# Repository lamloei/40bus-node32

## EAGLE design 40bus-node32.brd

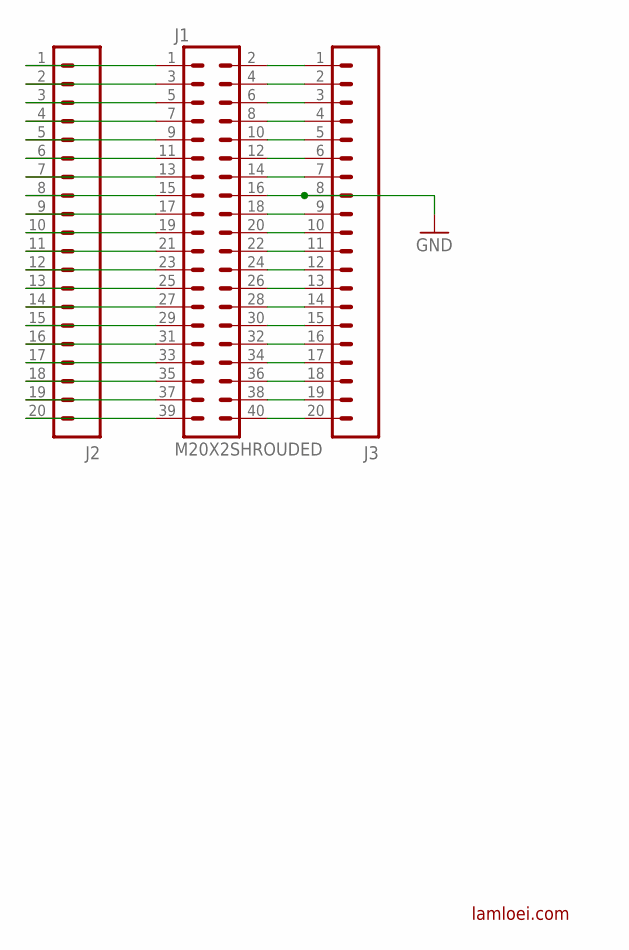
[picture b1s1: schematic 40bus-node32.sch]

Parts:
J1: M20X2SHROUDED; 2X20_SHROUDED
J2, J3: M20; 1X20
U$1: LAMLEOI_LOGO_3

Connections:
GND: J1.16, J3.8
unnamed: J1.2, J3.1
unnamed: J1.4, J3.2
unnamed: J1.6, J3.3
unnamed: J1.8, J3.4
unnamed: J1.10, J3.5
unnamed: J1.12, J3.6
unnamed: J1.14, J3.7
unnamed: J1.18, J3.9
unnamed: J1.20, J3.10
unnamed: J1.22, J3.11
unnamed: J1.24, J3.12
unnamed: J1.26, J3.13
unnamed: J1.28, J3.14
unnamed: J1.30, J3.15
unnamed: J1.32, J3.16
unnamed: J1.34, J3.17
unnamed: J1.36, J3.18
unnamed: J1.38, J3.19
unnamed: J1.40, J3.20
unnamed: J1.1, J2.1
unnamed: J1.3, J2.2
unnamed: J1.5, J2.3
unnamed: J1.7, J2.4
unnamed: J1.9, J2.5
unnamed: J1.11, J2.6
unnamed: J1.13, J2.7
unnamed: J1.15, J2.8
unnamed: J1.17, J2.9
unnamed: J1.19, J2.10
unnamed: J1.21, J2.11
unnamed: J1.23, J2.12
unnamed: J1.25, J2.13
unnamed: J1.27, J2.14
unnamed: J1.29, J2.15
unnamed: J1.31, J2.16
unnamed: J1.33, J2.17
unnamed: J1.35, J2.18
unnamed: J1.37, J2.19
unnamed: J1.39, J2.20

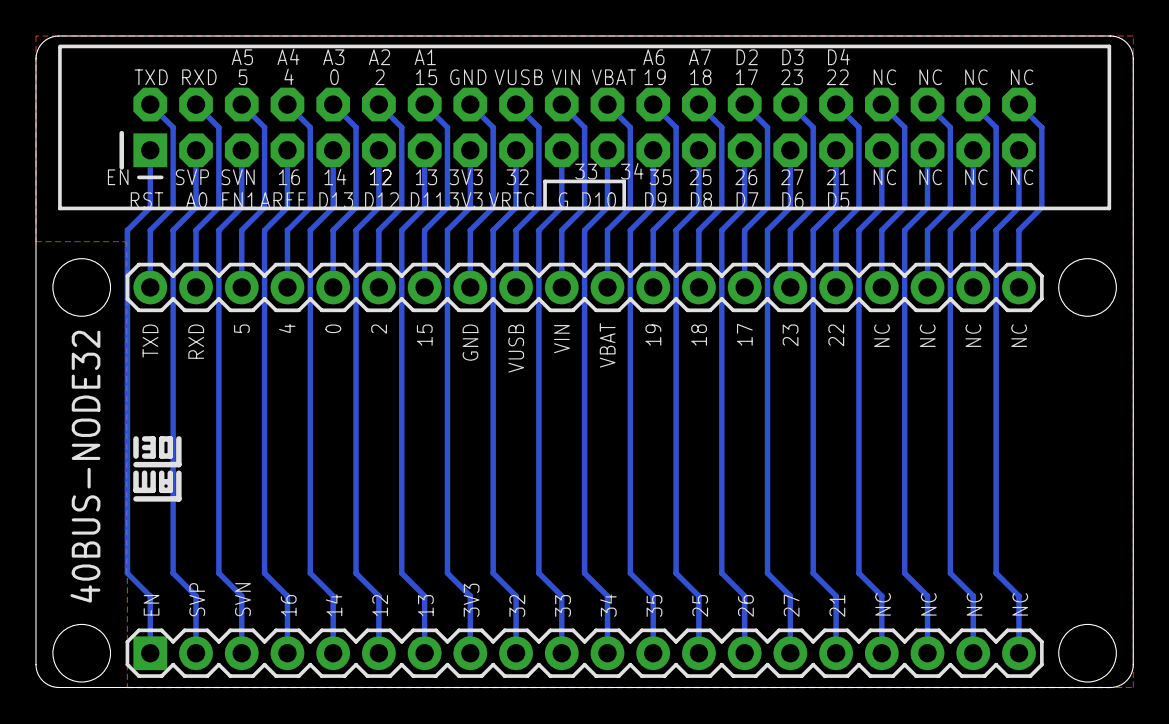
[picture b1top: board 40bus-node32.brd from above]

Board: 2 copper layers, 61.0 x 36.2 mm, 5 parts (1 on the bottom side), 40 nets.

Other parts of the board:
U$2: LAMLEOI_LOGO_3

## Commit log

2016-10-24 :tada: Added .gitattributes & .gitignore files
2016-10-24 40bus-node32
    40bus-node32

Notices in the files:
parts and their libraries:
SparkFun-Connectors: Licensing: Creative Commons ShareAlike 4.0 International - https://creativecommons.org/licenses/by-sa/4.0
